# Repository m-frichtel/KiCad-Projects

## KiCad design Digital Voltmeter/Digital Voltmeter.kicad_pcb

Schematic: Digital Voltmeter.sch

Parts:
C1: 470u; CP_Elec_10x10
C2: 2.2u; C_0603_1608Metric_Pad1.05x0.95mm_HandSolder
C3, C4: 10u; C_0603_1608Metric_Pad1.05x0.95mm_HandSolder
C5: 10nF; C_0603_1608Metric_Pad1.05x0.95mm_HandSolder
C6: 100nF; C_0603_1608Metric_Pad1.05x0.95mm_HandSolder
C7: 47nF; C_0603_1608Metric_Pad1.05x0.95mm_HandSolder
C8: 220nF; C_0603_1608Metric_Pad1.05x0.95mm_HandSolder
C9: 100pF; C_0603_1608Metric_Pad1.05x0.95mm_HandSolder
J1, J2: Conn_01x02_Male; PinHeader_1x02_P2.54mm_Vertical
R1: 1M; R_0603_1608Metric_Pad1.05x0.95mm_HandSolder
R2: 12k; R_0603_1608Metric_Pad1.05x0.95mm_HandSolder
R3: 470k; R_0603_1608Metric_Pad1.05x0.95mm_HandSolder
R4: 180k; R_0603_1608Metric_Pad1.05x0.95mm_HandSolder
R5: 22k; R_0603_1608Metric_Pad1.05x0.95mm_HandSolder
R6: 560; R_0603_1608Metric_Pad1.05x0.95mm_HandSolder
RV1: 20k; T93YB_TrimPot
U1: L78L05_SO8; SOIC-8_3.9x4.9mm_P1.27mm
U2: ICL7660S; SOIC127P600X175-8N
U3: ICL7107; ICL7107CPL&plus_
U4, U5, U6, U7: MAN6960; SC56-11SRWA

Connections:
5V: C2.1, R5.1, U1.1 (OUT), U1.5 (NC), U2.8, U3.1, U4.3, U5.3, U6.3, U7.3
-5V: C4.1, U2.5, U3.26
/Vin+: J1.1, R1.2
/Vin-: C5.1, J1.2, R2.1, RV1.1, U3.30, U3.32, U3.35
/Vin=9V: C1.1, J2.1, U1.4 (NC), U1.8 (IN)
GND: C1.2, C2.2, C4.2, J2.2, R6.2, U1.2 (GND), U1.3 (GND), U1.6 (GND), U1.7 (GND), U2.3, U3.21
unnamed: C3.1, U2.2
unnamed: C3.2, U2.4
unnamed: C5.2, R1.1, R2.2, U3.31
unnamed: C6.1, U3.33
unnamed: C6.2, U3.34
unnamed: C7.1, U3.29
unnamed: C7.2, C8.2, R3.2
unnamed: C8.1, U3.27
unnamed: C9.1, U3.38
unnamed: C9.2, R4.2, U3.40
unnamed: R3.1, U3.28
unnamed: R4.1, U3.39
unnamed: R5.2, RV1.3
unnamed: R6.1, U6.5
unnamed: RV1.2, U3.36
unnamed: U3.2, U7.2
unnamed: U3.3, U7.4
unnamed: U3.4, U7.6
unnamed: U3.5, U7.7
unnamed: U3.6, U7.9
unnamed: U3.7, U7.10
unnamed: U3.8, U7.1
unnamed: U3.9, U6.2
unnamed: U3.10, U6.4
unnamed: U3.11, U6.6
unnamed: U3.12, U6.7
unnamed: U3.13, U6.9
unnamed: U3.14, U6.1
unnamed: U3.15, U5.2
unnamed: U3.16, U5.6
unnamed: U3.17, U5.9
unnamed: U3.18, U5.1
unnamed: U3.19, U4.4, U4.6
unnamed: U3.20, U4.10
unnamed: U3.22, U5.10
unnamed: U3.23, U5.7
unnamed: U3.24, U5.4
unnamed: U3.25, U6.10

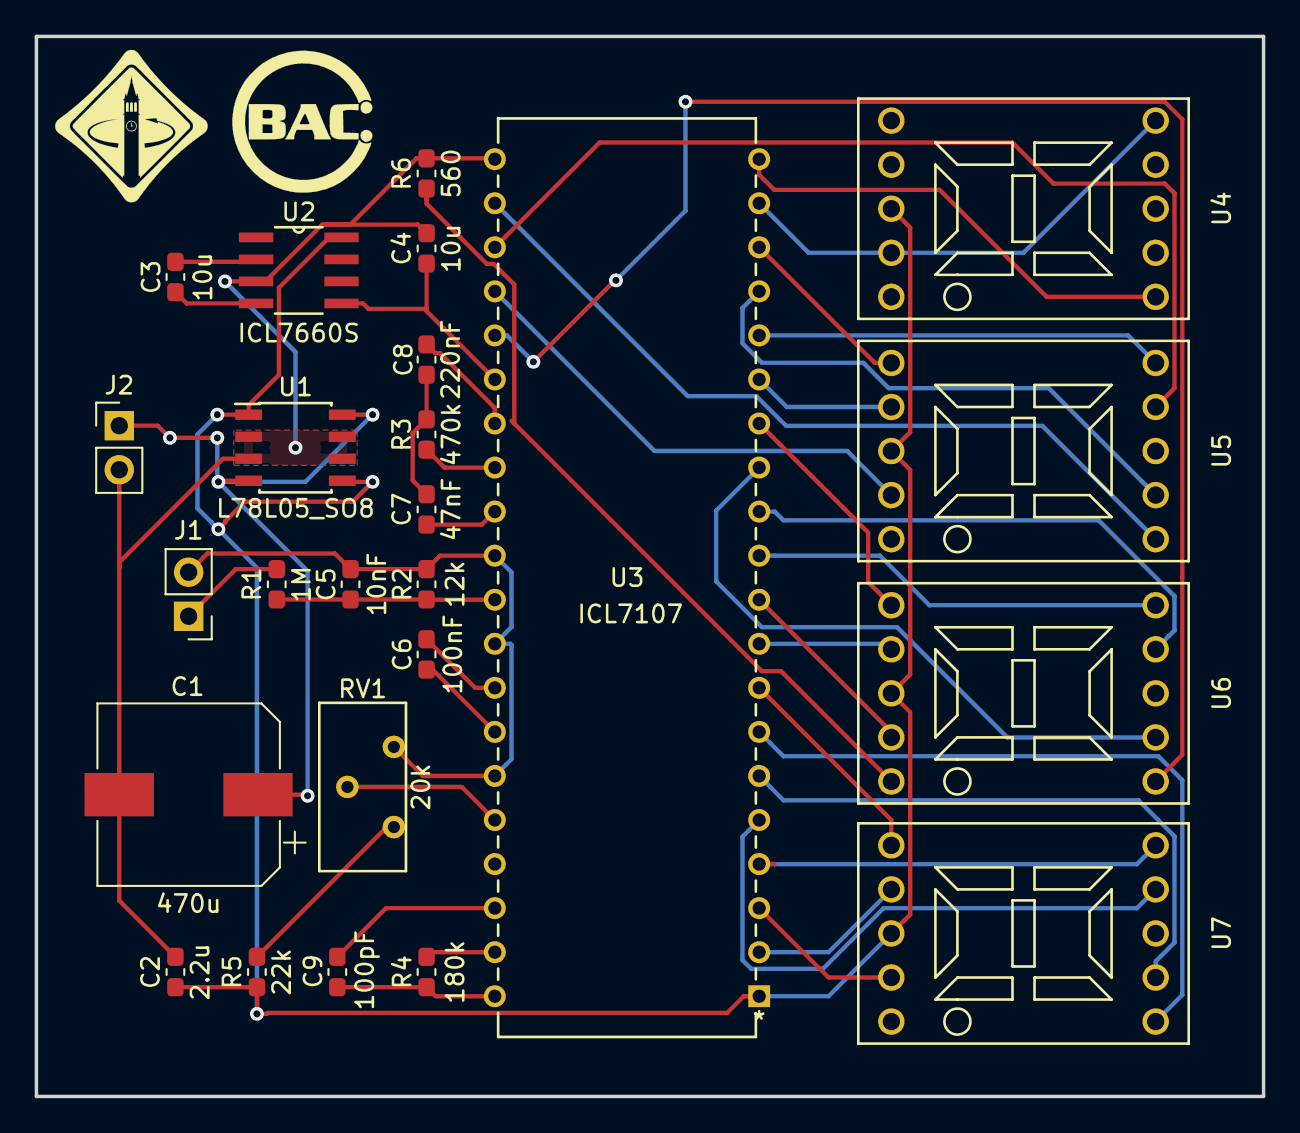
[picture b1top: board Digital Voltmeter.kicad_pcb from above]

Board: 2 copper layers, 70.8 x 61.1 mm, 25 parts (0 on the bottom side), 44 nets.

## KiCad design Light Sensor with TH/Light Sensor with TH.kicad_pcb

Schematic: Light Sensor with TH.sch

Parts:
C1: 1u; C_Axial_L3.8mm_D2.6mm_P7.50mm_Horizontal
D1: LED; LED_D5.0mm
J1: Conn_01x03; PinHeader_1x03_P2.54mm_Vertical
R1: 1k; R_Axial_DIN0309_L9.0mm_D3.2mm_P5.08mm_Vertical
R2: 1M; R_Axial_DIN0309_L9.0mm_D3.2mm_P5.08mm_Vertical
R3: 47k; R_Axial_DIN0309_L9.0mm_D3.2mm_P5.08mm_Vertical
RV1: R_POT; Potentiometer_Alps_RK09L_Single_Horizontal
U1, U2: LMC6482; DIP-4_W7.62mm

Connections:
+3V3: J1.3, RV1.1, U1.8 (V+), U2.8 (V+)
GND: D1.1, J1.1, R1.2, R2.2, RV1.3, U1.4 (V-), U2.4 (V-)
unnamed: C1.1, R3.1, U1.1, U1.5 (+)
unnamed: C1.2, R1.1, R3.2, U1.2 (-)
unnamed: D1.2, R2.1, U1.3 (+)
unnamed: RV1.2, U1.6 (-)

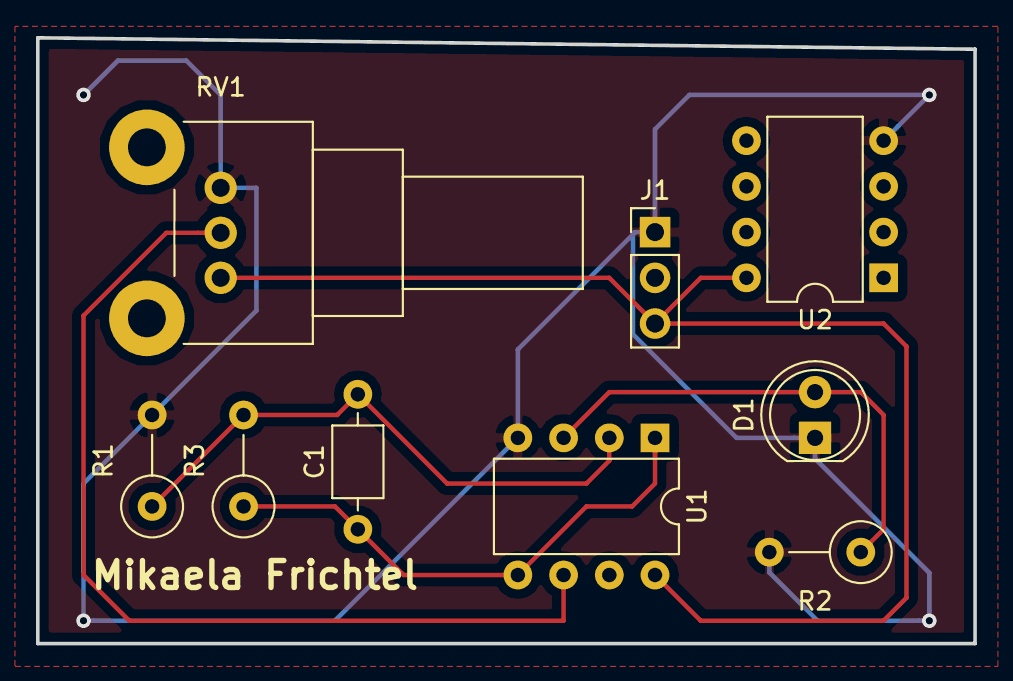
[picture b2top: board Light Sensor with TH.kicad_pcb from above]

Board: 2 copper layers, 52.1 x 33.7 mm, 9 parts (0 on the bottom side), 6 nets.

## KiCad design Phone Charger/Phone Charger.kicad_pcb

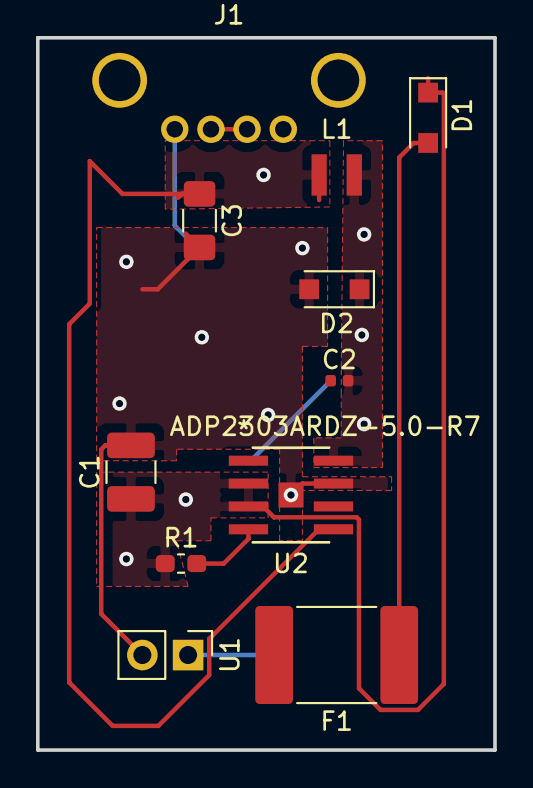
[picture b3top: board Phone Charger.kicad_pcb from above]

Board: 2 copper layers, 25.4 x 39.6 mm, 11 parts (0 on the bottom side), 9 nets.

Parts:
C1: 10 uF; C_1210_3225Metric_Pad1.42x2.65mm_HandSolder
C2: 0.1 uF; C_0402_1005Metric
C3: 47 uF; C_1206_3216Metric_Pad1.42x1.75mm_HandSolder
D1: D_Schottky; D_SOD-123F
D2: D1; D_SOD-123F
F1: Polyfuse; Fuse_2920_7451Metric_Pad2.10x5.45mm_HandSolder
J1: USB_A; USB-A-4Pos-THT
L1: 4.7 uH; IND-74438323047-SMD
R1: 100k; R_0603_1608Metric_Pad1.05x0.95mm_HandSolder
U1: PinHeader; PinHeader_1x02_P2.54mm_Vertical
U2: ADP2303ARDZ-5.0-R7; RD_8_1

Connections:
+12V: C1.1, D1.1, R1.1, U2.2, U2.3
GND: C1.2, C3.2, D2.2, J1.4, U1.2, U2.7, U2.EPAD
unnamed: C2.1, U2.1
unnamed: C2.2, D2.1, L1.1, U2.8
unnamed: D1.2, F1.1
unnamed: F1.2, U1.1
unnamed: J1.2, J1.3
unnamed: R1.2, U2.4
VBUS: C3.1, L1.2, U2.5

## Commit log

2018-10-15 Adding KiCad projects
2018-10-22 added schematic for digital voltmeter
2018-10-25 adding footprints
2018-11-01 working on pcb
2018-11-01 before changing some components
2018-11-01 replaced parts
2018-11-01 passing DMC

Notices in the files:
parts and their libraries:
Copyright 2016 Accelerated Designs. All rights reserved.
